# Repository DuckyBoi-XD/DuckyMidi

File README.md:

# DuckyMidi
The DuckyMidi is a Midi keyboard made from the mini midi magic guide which has a theme of Ducks

## Features

The DuckyMidi has all these features:

- 2 octaves for wide range of sounds
- LCD display for menu display
- 2 rotary knobs for menu/Midi control
- 12 macro keys
- Orpheus Pico microcontroller
- Gateron Pro black switches to feel like a piano key
- Manual on/off switch

## Inspiration

The DuckyMidi was created using the help of the guide from the mini midi magic and was created for many reasons. I'm experienced in music and when I saw the guide for the midi made me intreseted in making a Midi keyboard myself. This was also a great time to revise/practise my PCB designing and CAD modeling.

## Construction
The DuckyMidi is created with a custom PCB and case.

### PCB
The DuckyMidi's PCB:

### Case

The DuckyMidi's Case:

## BOM

| Component | Description | Quantity | Base Cost | Extra Costs | Link |
|-----------|-------------|----------|-----------|-------------|------|
| MCU | Raspberry Pi Pico Board RP2040 | 1 | $3.03 | (*GST*) | https://www.aliexpress.com/item/1005006087823796.html?spm=a2g0o.productlist.main.2.309b77b7b9P5jN&aem_p4p_detail=2025111416335911325003001759620000252286&algo_pvid=ee387e86-e232-4153-b3f9-458bd4187391&algo_exp_id=ee387e86-e232-4153-b3f9-458bd4187391-1&pdp_ext_f=%7B%22order%22%3A%22930%22%2C%22eval%22%3A%221%22%2C%22fromPage%22%3A%22search%22%7D&pdp_npi=6%40dis%21USD%212.89%212.63%21%21%2120.42%2118.62%21%402101e80f17631668397588042e85f8%2112000044713099471%21sea%21NZ%216394433987%21X%211%210%21n_tag%3A-29911%3Bd%3A53947009%3Bm03_new_user%3A-29895&curPageLogUid=tcKrQuvSvlbc&utparam-url=scene%3Asearch%7Cquery_from%3A%7Cx_object_id%3A1005006087823796%7C_p_origin_prod%3A&search_p4p_id=2025111416335911325003001759620000252286_1 |
| Rotary Encoder | Rotary Encoder EC11 w Push Button 5px | 1 | $2.78 | (*GST*) | https://www.aliexpress.com/item/1005005983134515.html?spm=a2g0o.productlist.main.2.7b8b2af8yrmzbn&algo_pvid=0aa5a70e-55d7-4d0a-942b-b23015df3345&algo_exp_id=0aa5a70e-55d7-4d0a-942b-b23015df3345-1&pdp_ext_f=%7B%22order%22%3A%221803%22%2C%22eval%22%3A%221%22%2C%22fromPage%22%3A%22search%22%7D&pdp_npi=6%40dis%21USD%212.73%212.72%21%21%212.73%212.72%21%402103123917631656330543244e4ccf%2112000035172713577%21sea%21NZ%216394433987%21X%211%210%21n_tag%3A-29911%3Bd%3A53947009%3Bm03_new_user%3A-29895%3BpisId%3A5000000193061256&curPageLogUid=zw64DmhjwP3R&utparam-url=scene%3Asearch%7Cquery_from%3A%7Cx_object_id%3A1005005983134515%7C_p_origin_prod%3A |
| Rotary Encoder Knob | Aluminum alloy knob cap x2 | 1 | $2.70 | $3.58 +(*GST*)| https://www.aliexpress.com/item/1005006912587864.html?spm=a2g0o.productlist.main.13.7e1d7f61dMasto&algo_pvid=33504228-93a7-4935-8ff3-1f5bbeadf0bb&algo_exp_id=33504228-93a7-4935-8ff3-1f5bbeadf0bb-9&pdp_ext_f=%7B%22order%22%3A%2266%22%2C%22eval%22%3A%221%22%2C%22fromPage%22%3A%22search%22%7D&pdp_npi=6%40dis%21USD%212.70%211.86%21%21%2119.06%2113.15%21%402101c59117631691828366706ee5bb%2112000038705419962%21sea%21NZ%216394433987%21X%211%210%21n_tag%3A-29911%3Bd%3A53947009%3Bm03_new_user%3A-29895&curPageLogUid=zdhAQMLQWEjD&utparam-url=scene%3Asearch%7Cquery_from%3A%7Cx_object_id%3A1005006912587864%7C_p_origin_prod%3A |
| Switches Piano | Outemu Switch Mechanical Keyboard Switch Black 70 pcs | 1 | $9.19 | (*GST*) | https://www.aliexpress.com/item/1005002378701948.html?spm=a2g0o.productlist.main.29.24d4fh40fh40Io&algo_pvid=a82f2df0-df86-4c28-b7ec-0d8a91854ad8&algo_exp_id=a82f2df0-df86-4c28-b7ec-0d8a91854ad8-26&pdp_ext_f=%7B%22order%22%3A%221870%22%2C%22eval%22%3A%221%22%2C%22fromPage%22%3A%22search%22%7D&pdp_npi=6%40dis%21USD%213.12%212.85%21%21%213.12%212.85%21%402103128817631109182464803e060d%2112000020915533393%21sea%21NZ%216394433987%21X%211%210%21n_tag%3A-29911%3Bd%3A53947009%3Bm03_new_user%3A-29895&curPageLogUid=p8GAhwpPO6Oo&utparam-url=scene%3Asearch%7Cquery_from%3A%7Cx_object_id%3A1005002378701948%7C_p_origin_prod%3A |
| Keycaps White | 10pcs DSA Keycap Set PBT Blank Keycaps 1.5U | 2 | $7.50 | (*GST*) | https://www.aliexpress.com/item/1005009077100804.html?spm=a2g0o.productlist.main.4.199252d1ns9WNs&algo_pvid=421e2164-0285-4bb4-a4f6-f57fc641a06b&algo_exp_id=421e2164-0285-4bb4-a4f6-f57fc641a06b-3&pdp_ext_f=%7B%22order%22%3A%2270%22%2C%22eval%22%3A%221%22%2C%22fromPage%22%3A%22search%22%7D&pdp_npi=6%40dis%21USD%213.47%213.47%21%21%213.47%213.47%21%40210319b017631822695843780e69f4%2112000047831760843%21sea%21NZ%216394433987%21X%211%210%21n_tag%3A-29911%3Bd%3A53947009%3Bm03_new_user%3A-29895&curPageLogUid=RocAxgbWRvrD&utparam-url=scene%3Asearch%7Cquery_from%3A%7Cx_object_id%3A1005009077100804%7C_p_origin_prod%3A |
| Keycaps Black | Customized PBT Blank Keycaps DSA 1.25U 10 pcs | 1 | $3.77 | (*GST*) | https://www.aliexpress.com/item/1005006080902747.html?spm=a2g0o.productlist.main.26.699a3ff62WoceG&algo_pvid=3a42afee-cf12-4b9f-a9c1-569b2a63ded9&algo_exp_id=3a42afee-cf12-4b9f-a9c1-569b2a63ded9-23&pdp_ext_f=%7B%22order%22%3A%2212%22%2C%22eval%22%3A%221%22%2C%22fromPage%22%3A%22search%22%7D&pdp_npi=6%40dis%21USD%213.66%213.66%21%21%213.66%213.66%21%402101e62517631820795884833e666d%2112000035643469885%21sea%21NZ%216394433987%21X%211%210%21n_tag%3A-29911%3Bd%3A53947009%3Bm03_new_user%3A-29895&curPageLogUid=NbvIijfb90bX&utparam-url=scene%3Asearch%7Cquery_from%3A%7Cx_object_id%3A1005006080902747%7C_p_origin_prod%3A |
| Keycaps Macro | YMDK MOA Profile 1u Keycaps Dark Blue 25pcs | 1 | $5.77 | (*GST*) | https://www.aliexpress.com/item/1005008795444732.html?spm=a2g0o.detail.pcDetailTopMoreOtherSeller.7.6155Oxq5Oxq5g2&gps-id=pcDetailTopMoreOtherSeller&scm=1007.40196.439370.0&scm_id=1007.40196.439370.0&scm-url=1007.40196.439370.0&pvid=3c3f9d66-ba11-4bbf-9a26-8683f9403fb6&_t=gps-id:pcDetailTopMoreOtherSeller,scm-url:1007.40196.439370.0,pvid:3c3f9d66-ba11-4bbf-9a26-8683f9403fb6,tpp_buckets:668%232846%238108%231977&pdp_ext_f=%7B%22order%22%3A%22161%22%2C%22eval%22%3A%221%22%2C%22sceneId%22%3A%2230050%22%2C%22fromPage%22%3A%22recommend%22%7D&pdp_npi=6%40dis%21USD%213.09%212.39%21%21%213.09%212.39%21%402101c44f17631625120246447ec4f0%2112000046697462934%21rec%21NZ%216394433987%21XZ%211%210%21n_tag%3A-29911%3Bd%3A53947009%3Bm03_new_user%3A-29895&utparam-url=scene%3ApcDetailTopMoreOtherSeller%7Cquery_from%3A%7Cx_object_id%3A1005008795444732%7C_p_origin_prod%3A |
| On Off Switch | Push Button Switch 21x15mm SPST 2Pin 6A 250V 5pcs | 1 | $1.97 | (*GST*) | https://www.aliexpress.com/item/1005007945027854.html?spm=a2g0o.productlist.main.12.3150mcAamcAa7L&algo_pvid=32afb5ff-8f5c-4864-b5c3-2deac9203239&algo_exp_id=32afb5ff-8f5c-4864-b5c3-2deac9203239-11&pdp_ext_f=%7B%22order%22%3A%22931%22%2C%22eval%22%3A%221%22%2C%22fromPage%22%3A%22search%22%7D&pdp_npi=6%40dis%21USD%212.86%212.74%21%21%2120.19%2119.34%21%402101e83017631444954975684e6bd0%2112000042962125991%21sea%21NZ%216394433987%21X%211%210%21n_tag%3A-29911%3Bd%3A53947009%3Bm03_new_user%3A-29895%3BpisId%3A5000000193061260&curPageLogUid=Vng3iI0yCpsS&utparam-url=scene%3Asearch%7Cquery_from%3A%7Cx_object_id%3A1005007945027854%7C_p_origin_prod%3A |
| Diodes | 1N4148 DO-35 100pcs | 1 | $2.51 | (*GST*) | https://www.aliexpress.com/item/1005009896621714.html?spm=a2g0o.productlist.main.2.b6034ca2LXgpnV&aem_p4p_detail=202511141542021206520124664960000242848&algo_pvid=8a62d6d5-45a8-40cc-8c25-0ffc62db9ec1&algo_exp_id=8a62d6d5-45a8-40cc-8c25-0ffc62db9ec1-1&pdp_ext_f=%7B%22order%22%3A%22167%22%2C%22eval%22%3A%221%22%2C%22fromPage%22%3A%22search%22%7D&pdp_npi=6%40dis%21USD%212.51%212.33%21%21%2117.72%2116.48%21%402103119c17631637220798809eedd6%2112000050510129669%21sea%21NZ%216394433987%21X%211%210%21n_tag%3A-29911%3Bd%3A53947009%3Bm03_new_user%3A-29895&curPageLogUid=uuyJszEGKD0D&utparam-url=scene%3Asearch%7Cquery_from%3A%7Cx_object_id%3A1005009896621714%7C_p_origin_prod%3A&search_p4p_id=202511141542021206520124664960000242848_1 |
| Pin Header | Pin Header 2.0MM/2.54MM Pitch Row Female/Male, Single Row 1x40P | 1 | $3.24 | (*GST*) | https://www.aliexpress.com/item/4001122376295.html?spm=a2g0o.productlist.main.7.4938609eYgDUkM&algo_pvid=89f98918-4419-4569-9643-dcb57d427f70&algo_exp_id=89f98918-4419-4569-9643-dcb57d427f70-8&pdp_ext_f=%7B%22order%22%3A%221865%22%2C%22eval%22%3A%221%22%2C%22fromPage%22%3A%22search%22%7D&pdp_npi=6%40dis%21USD%212.86%212.64%21%21%212.86%212.64%21%402101e2b417631677681774044eccae%2110000014593481347%21sea%21NZ%216394433987%21X%211%210%21n_tag%3A-29911%3Bd%3A53947009%3Bm03_new_user%3A-29895&curPageLogUid=15XEU1QMwrxO&utparam-url=scene%3Asearch%7Cquery_from%3A%7Cx_object_id%3A4001122376295%7C_p_origin_prod%3A |
| DAC | PCM5100APWR 5pcs | 1 | $2.13 | (*GST*) | https://www.aliexpress.com/item/1005008173380058.html?spm=a2g0o.productlist.main.13.6ec8135cA6drR5&algo_pvid=42d23cc0-c66c-473f-a405-e27b6ae6f3c9&algo_exp_id=42d23cc0-c66c-473f-a405-e27b6ae6f3c9-10&pdp_ext_f=%7B%22order%22%3A%2222%22%2C%22eval%22%3A%221%22%2C%22fromPage%22%3A%22search%22%7D&pdp_npi=6%40dis%21USD%212.13%211.98%21%21%212.13%211.98%21%402101eede17631661586404422e35ce%2112000044104050969%21sea%21NZ%216394433987%21X%211%210%21n_tag%3A-29911%3Bd%3A53947009%3Bm03_new_user%3A-29895&curPageLogUid=G8fdJ97Ygiqn&utparam-url=scene%3Asearch%7Cquery_from%3A%7Cx_object_id%3A1005008173380058%7C_p_origin_prod%3A |
| LCD/SD Card port | LCD Module Display | 1 | $3.30 | $3.87 +(*GST*)| https://www.aliexpress.com/item/1005003633248802.html?spm=a2g0o.productlist.main.1.339e5587mdfYG4&algo_pvid=8ccd60b3-f852-45ba-9fa8-ed2a46929b25&algo_exp_id=8ccd60b3-f852-45ba-9fa8-ed2a46929b25-0&pdp_ext_f=%7B%22order%22%3A%2214%22%2C%22eval%22%3A%221%22%2C%22fromPage%22%3A%22search%22%7D&pdp_npi=6%40dis%21USD%213.30%212.05%21%21%213.30%212.05%21%402103128817631664477745451e0623%2112000026581177505%21sea%21NZ%216394433987%21X%211%210%21n_tag%3A-29911%3Bd%3A53947009%3Bm03_new_user%3A-29895&curPageLogUid=4gMrdLkJL4NF&utparam-url=scene%3Asearch%7Cquery_from%3A%7Cx_object_id%3A1005003633248802%7C_p_origin_prod%3A |
| Jumper Wires | Dupont Line Female To Female | 1 | $2.87 | (*GST*) | https://www.aliexpress.com/item/1005006994502819.html?spm=a2g0o.productlist.main.4.7a3653e8zRQeRH&algo_pvid=820b4a27-b4ed-4fb3-a2f5-2936927aabf5&algo_exp_id=820b4a27-b4ed-4fb3-a2f5-2936927aabf5-3&pdp_ext_f=%7B%22order%22%3A%227328%22%2C%22eval%22%3A%221%22%2C%22orig_sl_item_id%22%3A%221005006994502819%22%2C%22orig_item_id%22%3A%221005007851913589%22%2C%22fromPage%22%3A%22search%22%7D&pdp_npi=6%40dis%21USD%212.74%211.25%21%21%2119.36%218.83%21%40210319b017631716593444599e69fc%2112000051967607984%21sea%21NZ%216394433987%21X%211%210%21n_tag%3A-29911%3Bd%3A53947009%3Bm03_new_user%3A-29895%3BpisId%3A5000000193373821&curPageLogUid=zizVsMG2LrFv&utparam-url=scene%3Asearch%7Cquery_from%3A%7Cx_object_id%3A1005006994502819%7C_p_origin_prod%3A1005007851913589 |
| Heat insert | Brass Copper Embed Insert Nut 50pc M3 (OD 4.2mm) 4mm | 1 | $2.43 | (*GST*) | https://www.aliexpress.com/item/1005007654176205.html?spm=a2g0o.detail.pcDetailTopMoreOtherSeller.11.1b24RY8fRY8fV3&gps-id=pcDetailTopMoreOtherSeller&scm=1007.14452.396806.0&scm_id=1007.14452.396806.0&scm-url=1007.14452.396806.0&pvid=b34a5f57-fcce-4a45-9604-6228827ab757&_t=gps-id:pcDetailTopMoreOtherSeller,scm-url:1007.14452.396806.0,pvid:b34a5f57-fcce-4a45-9604-6228827ab757,tpp_buckets:668%232846%238108%231977&pdp_ext_f=%7B%22order%22%3A%22360%22%2C%22eval%22%3A%221%22%2C%22sceneId%22%3A%2230050%22%2C%22fromPage%22%3A%22recommend%22%7D&pdp_npi=6%40dis%21USD%211.99%211.90%21%21%211.99%211.90%21%402101d9ef17631744175183084e88a2%2112000041671883302%21rec%21NZ%216394433987%21XZ%211%210%21n_tag%3A-29911%3Bd%3A53947009%3Bm03_new_user%3A-29895&utparam-url=scene%3ApcDetailTopMoreOtherSeller%7Cquery_from%3A%7Cx_object_id%3A1005007654176205%7C_p_origin_prod%3A&search_p4p_id=202511141840175552440462087719283089_2 |
| M3 Screw | Stainless Steel Laptop Computer Cross Phillips 50pc M3 14mm | 1 | $3.32 | (*GST*) | https://www.aliexpress.com/item/4001248931159.html?spm=a2g0o.productlist.main.4.1ab3c14eB334N5&algo_pvid=9123c1ac-77a9-4710-ab36-97dca0a2b565&algo_exp_id=9123c1ac-77a9-4710-ab36-97dca0a2b565-3&pdp_ext_f=%7B%22order%22%3A%221522%22%2C%22eval%22%3A%221%22%2C%22fromPage%22%3A%22search%22%7D&pdp_npi=6%40dis%21USD%211.68%211.59%21%21%211.68%211.59%21%402101df0e17631771527526971e99ca%2112000034160900239%21sea%21NZ%216394433987%21X%211%210%21n_tag%3A-29911%3Bd%3A53947009%3Bm03_new_user%3A-29895&curPageLogUid=KvbKqaCNqWL5&utparam-url=scene%3Asearch%7Cquery_from%3A%7Cx_object_id%3A4001248931159%7C_p_origin_prod%3A |
| PCB | JLCPCB PCB | 5 | $32.40 | (*GST*) | N/A |
| **Total** | | | **$96.36** | |

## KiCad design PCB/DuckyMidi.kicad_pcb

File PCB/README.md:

### This is a PCB files of the project

The production file is the file that I would send to the manufacturer

The rest is just the kicad files

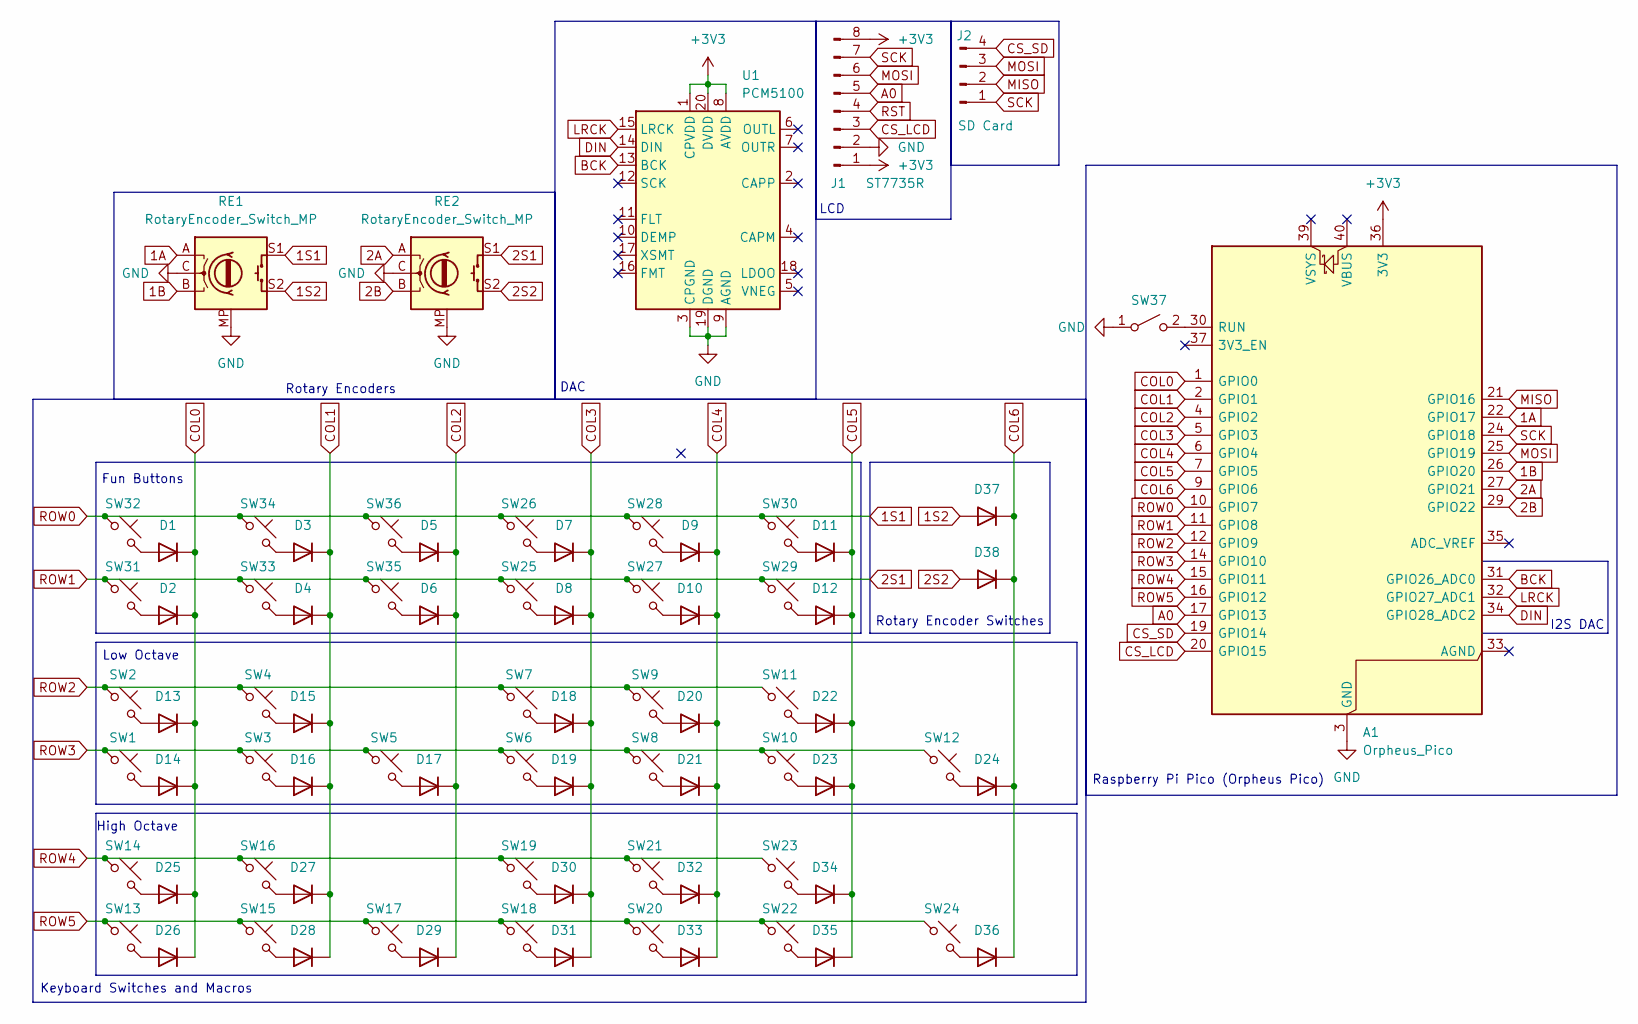
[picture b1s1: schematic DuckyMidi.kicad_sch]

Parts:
A1: Orpheus_Pico; RaspberryPi_Pico_Common_Unspecified
D1, D2, D3, D4, D5, D6, D7, D8, D9, D10, D11, D12, D13, D14, D15, D16, D17, D18, D19, D20, D21, D22, D23, D24, D25, D26, D27, D28, D29, D30, D31, D32, D33, D34, D35, D36, D37, D38: 1N4148; D_DO-35_SOD27_P7.62mm_Horizontal
J1: ST7735R; PinHeader_1x08_P2.54mm_Vertical
J2: SD Card; PinHeader_1x04_P2.54mm_Vertical
RE1, RE2: RotaryEncoder_Switch_MP; RotaryEncoder_Alps_EC11E-Switch_Vertical_H20mm_MountingHoles
SW1, SW2, SW3, SW4, SW5, SW6, SW7, SW8, SW9, SW10, SW11, SW12, SW13, SW14, SW15, SW16, SW17, SW18, SW19, SW20, SW21, SW22, SW23, SW24, SW25, SW26, SW27, SW28, SW29, SW30, SW31, SW32, SW33, SW34, SW35, SW36: SW_Push_45deg; MX_PCB_1.00u
SW37: SW_SPST; PinHeader_1x02_P2.54mm_Vertical
U1: PCM5100; TSSOP-20_4.4x6.5mm_P0.65mm

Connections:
1A: A1.22 (GPIO17), RE1.A
1B: A1.26 (GPIO20), RE1.B
1S1: A1.10 (GPIO7), RE1.S1, SW26.1, SW28.1, SW30.1, SW32.1, SW34.1, SW36.1
1S2: D37.2 (A), RE1.S2
2A: A1.27 (GPIO21), RE2.A
2B: A1.29 (GPIO22), RE2.B
2S1: A1.11 (GPIO8), RE2.S1, SW25.1, SW27.1, SW29.1, SW31.1, SW33.1, SW35.1
2S2: D38.2 (A), RE2.S2
+3V3: A1.36 (3V3), J1.1, J1.8, U1.1 (CPVDD), U1.8 (AVDD), U1.20 (DVDD)
A0: A1.17 (GPIO13), J1.5
BCK: A1.31 (GPIO26_ADC0), U1.13 (BCK)
COL0: A1.1 (GPIO0), D1.1 (K), D2.1 (K), D13.1 (K), D14.1 (K), D25.1 (K), D26.1 (K)
COL1: A1.2 (GPIO1), D3.1 (K), D4.1 (K), D15.1 (K), D16.1 (K), D27.1 (K), D28.1 (K)
COL2: A1.4 (GPIO2), D5.1 (K), D6.1 (K), D17.1 (K), D29.1 (K)
COL3: A1.5 (GPIO3), D7.1 (K), D8.1 (K), D18.1 (K), D19.1 (K), D30.1 (K), D31.1 (K)
COL4: A1.6 (GPIO4), D9.1 (K), D10.1 (K), D20.1 (K), D21.1 (K), D32.1 (K), D33.1 (K)
COL5: A1.7 (GPIO5), D11.1 (K), D12.1 (K), D22.1 (K), D23.1 (K), D34.1 (K), D35.1 (K)
COL6: A1.9 (GPIO6), D24.1 (K), D36.1 (K), D37.1 (K), D38.1 (K)
CS_LCD: A1.20 (GPIO15), J1.3
CS_SD: A1.19 (GPIO14), J2.4
DIN: A1.34 (GPIO28_ADC2), U1.14 (DIN)
GND: A1.3 (GND), A1.8 (GND), A1.13 (GND), A1.18 (GND), A1.23 (GND), A1.28 (GND), A1.38 (GND), J1.2, RE1.C, RE1.MP, RE2.C, RE2.MP, SW37.1 (A), U1.3 (CPGND), U1.9 (AGND), U1.19 (DGND)
LRCK: A1.32 (GPIO27_ADC1), U1.15 (LRCK)
MISO: A1.21 (GPIO16), J2.2
MOSI: A1.25 (GPIO19), J1.6, J2.3
unnamed: A1.30 (RUN), SW37.2 (B)
unnamed: D1.2 (A), SW32.2
unnamed: D2.2 (A), SW31.2
unnamed: D3.2 (A), SW34.2
unnamed: D4.2 (A), SW33.2
unnamed: D5.2 (A), SW36.2
unnamed: D6.2 (A), SW35.2
unnamed: D7.2 (A), SW26.2
unnamed: D8.2 (A), SW25.2
unnamed: D9.2 (A), SW28.2
unnamed: D10.2 (A), SW27.2
unnamed: D11.2 (A), SW30.2
unnamed: D12.2 (A), SW29.2
unnamed: D13.2 (A), SW2.2
unnamed: D14.2 (A), SW1.2
unnamed: D15.2 (A), SW4.2
unnamed: D16.2 (A), SW3.2
unnamed: D17.2 (A), SW5.2
unnamed: D18.2 (A), SW7.2
unnamed: D19.2 (A), SW6.2
unnamed: D20.2 (A), SW9.2
unnamed: D21.2 (A), SW8.2
unnamed: D22.2 (A), SW11.2
unnamed: D23.2 (A), SW10.2
unnamed: D24.2 (A), SW12.2
unnamed: D25.2 (A), SW14.2
unnamed: D26.2 (A), SW13.2
unnamed: D27.2 (A), SW16.2
unnamed: D28.2 (A), SW15.2
unnamed: D29.2 (A), SW17.2
unnamed: D30.2 (A), SW19.2
unnamed: D31.2 (A), SW18.2
unnamed: D32.2 (A), SW21.2
unnamed: D33.2 (A), SW20.2
unnamed: D34.2 (A), SW23.2
unnamed: D35.2 (A), SW22.2
unnamed: D36.2 (A), SW24.2
ROW2: A1.12 (GPIO9), SW2.1, SW4.1, SW7.1, SW9.1, SW11.1
ROW3: A1.14 (GPIO10), SW1.1, SW3.1, SW5.1, SW6.1, SW8.1, SW10.1, SW12.1
ROW4: A1.15 (GPIO11), SW14.1, SW16.1, SW19.1, SW21.1, SW23.1
ROW5: A1.16 (GPIO12), SW13.1, SW15.1, SW17.1, SW18.1, SW20.1, SW22.1, SW24.1
RST: J1.4
SCK: A1.24 (GPIO18), J1.7, J2.1

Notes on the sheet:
DAC
Rotary Encoders
Low Octave
High Octave
Rotary Encoder Switches
I2S DAC
LCD
Raspberry Pi Pico (Orpheus Pico)
Fun Buttons
Keyboard Switches and Macros

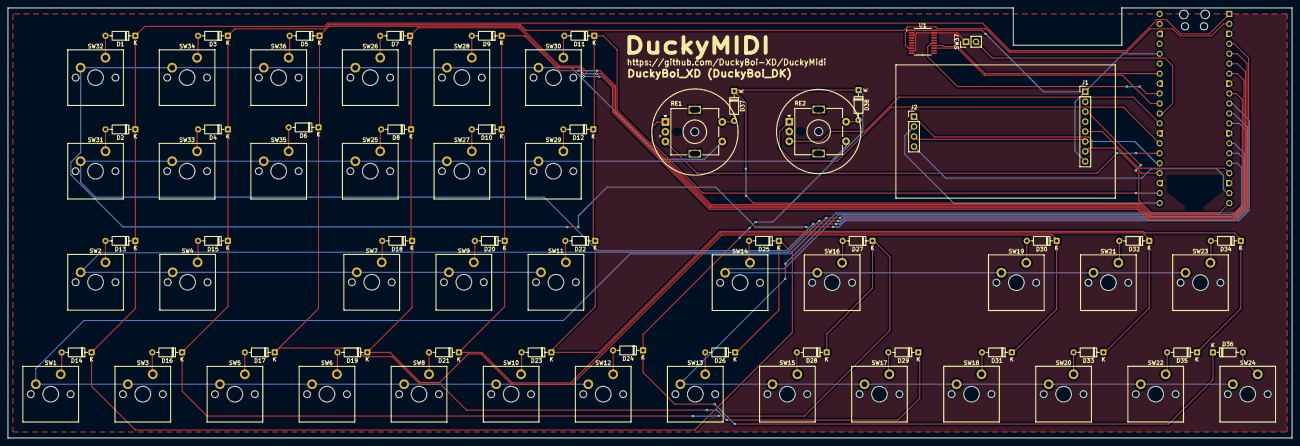
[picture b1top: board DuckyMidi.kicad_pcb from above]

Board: 2 copper layers, 327.7 x 109.7 mm, 81 parts (1 on the bottom side), 67 nets.

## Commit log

2025-11-14 Add project title to README.md
2025-11-14 Add GNU GPL v3 license file
    Added the GNU General Public License version 3 to the project.
2025-11-14 Added Nov 14 - Schematics work
    Document project details and initial progress on the DuckyMidi MIDI keyboard.
2025-11-15 Add entry for November 15th PCB editor
    Documented progress on PCB design and component placement.
2025-11-30 Update README with DuckyMidi details
    Added detailed description, features, and construction information for the DuckyMidi.
2025-11-30 Add README for CAD model files
2025-11-30 Update README formatting and add headings
2025-11-30 Update README to remove unnecessary information
    Removed redundant line about CAD model file.
2025-11-30 Create README.md for PCB project files
    Add README to explain PCB files and production process
2025-11-30 Create temp
2025-11-30 Add README for Bill Of Materials
2025-11-30 Add inspiration section to README
    Added an inspiration section detailing the motivation behind creating the DuckyMidi.
2025-11-30 Add BOM section with component details
    Added a Bill of Materials (BOM) section with component details.
2025-11-30 Added BOM to READEME.md
2025-11-30 Add GST details to BOM components
    Added GST information to various components in the BOM.
2025-11-30 Add PCB CAD model information to README
2025-11-30 Revise component list and update PCB pricing
    Updated the components list and their prices in the README file, including a change in the quantity and price of the PCB.
